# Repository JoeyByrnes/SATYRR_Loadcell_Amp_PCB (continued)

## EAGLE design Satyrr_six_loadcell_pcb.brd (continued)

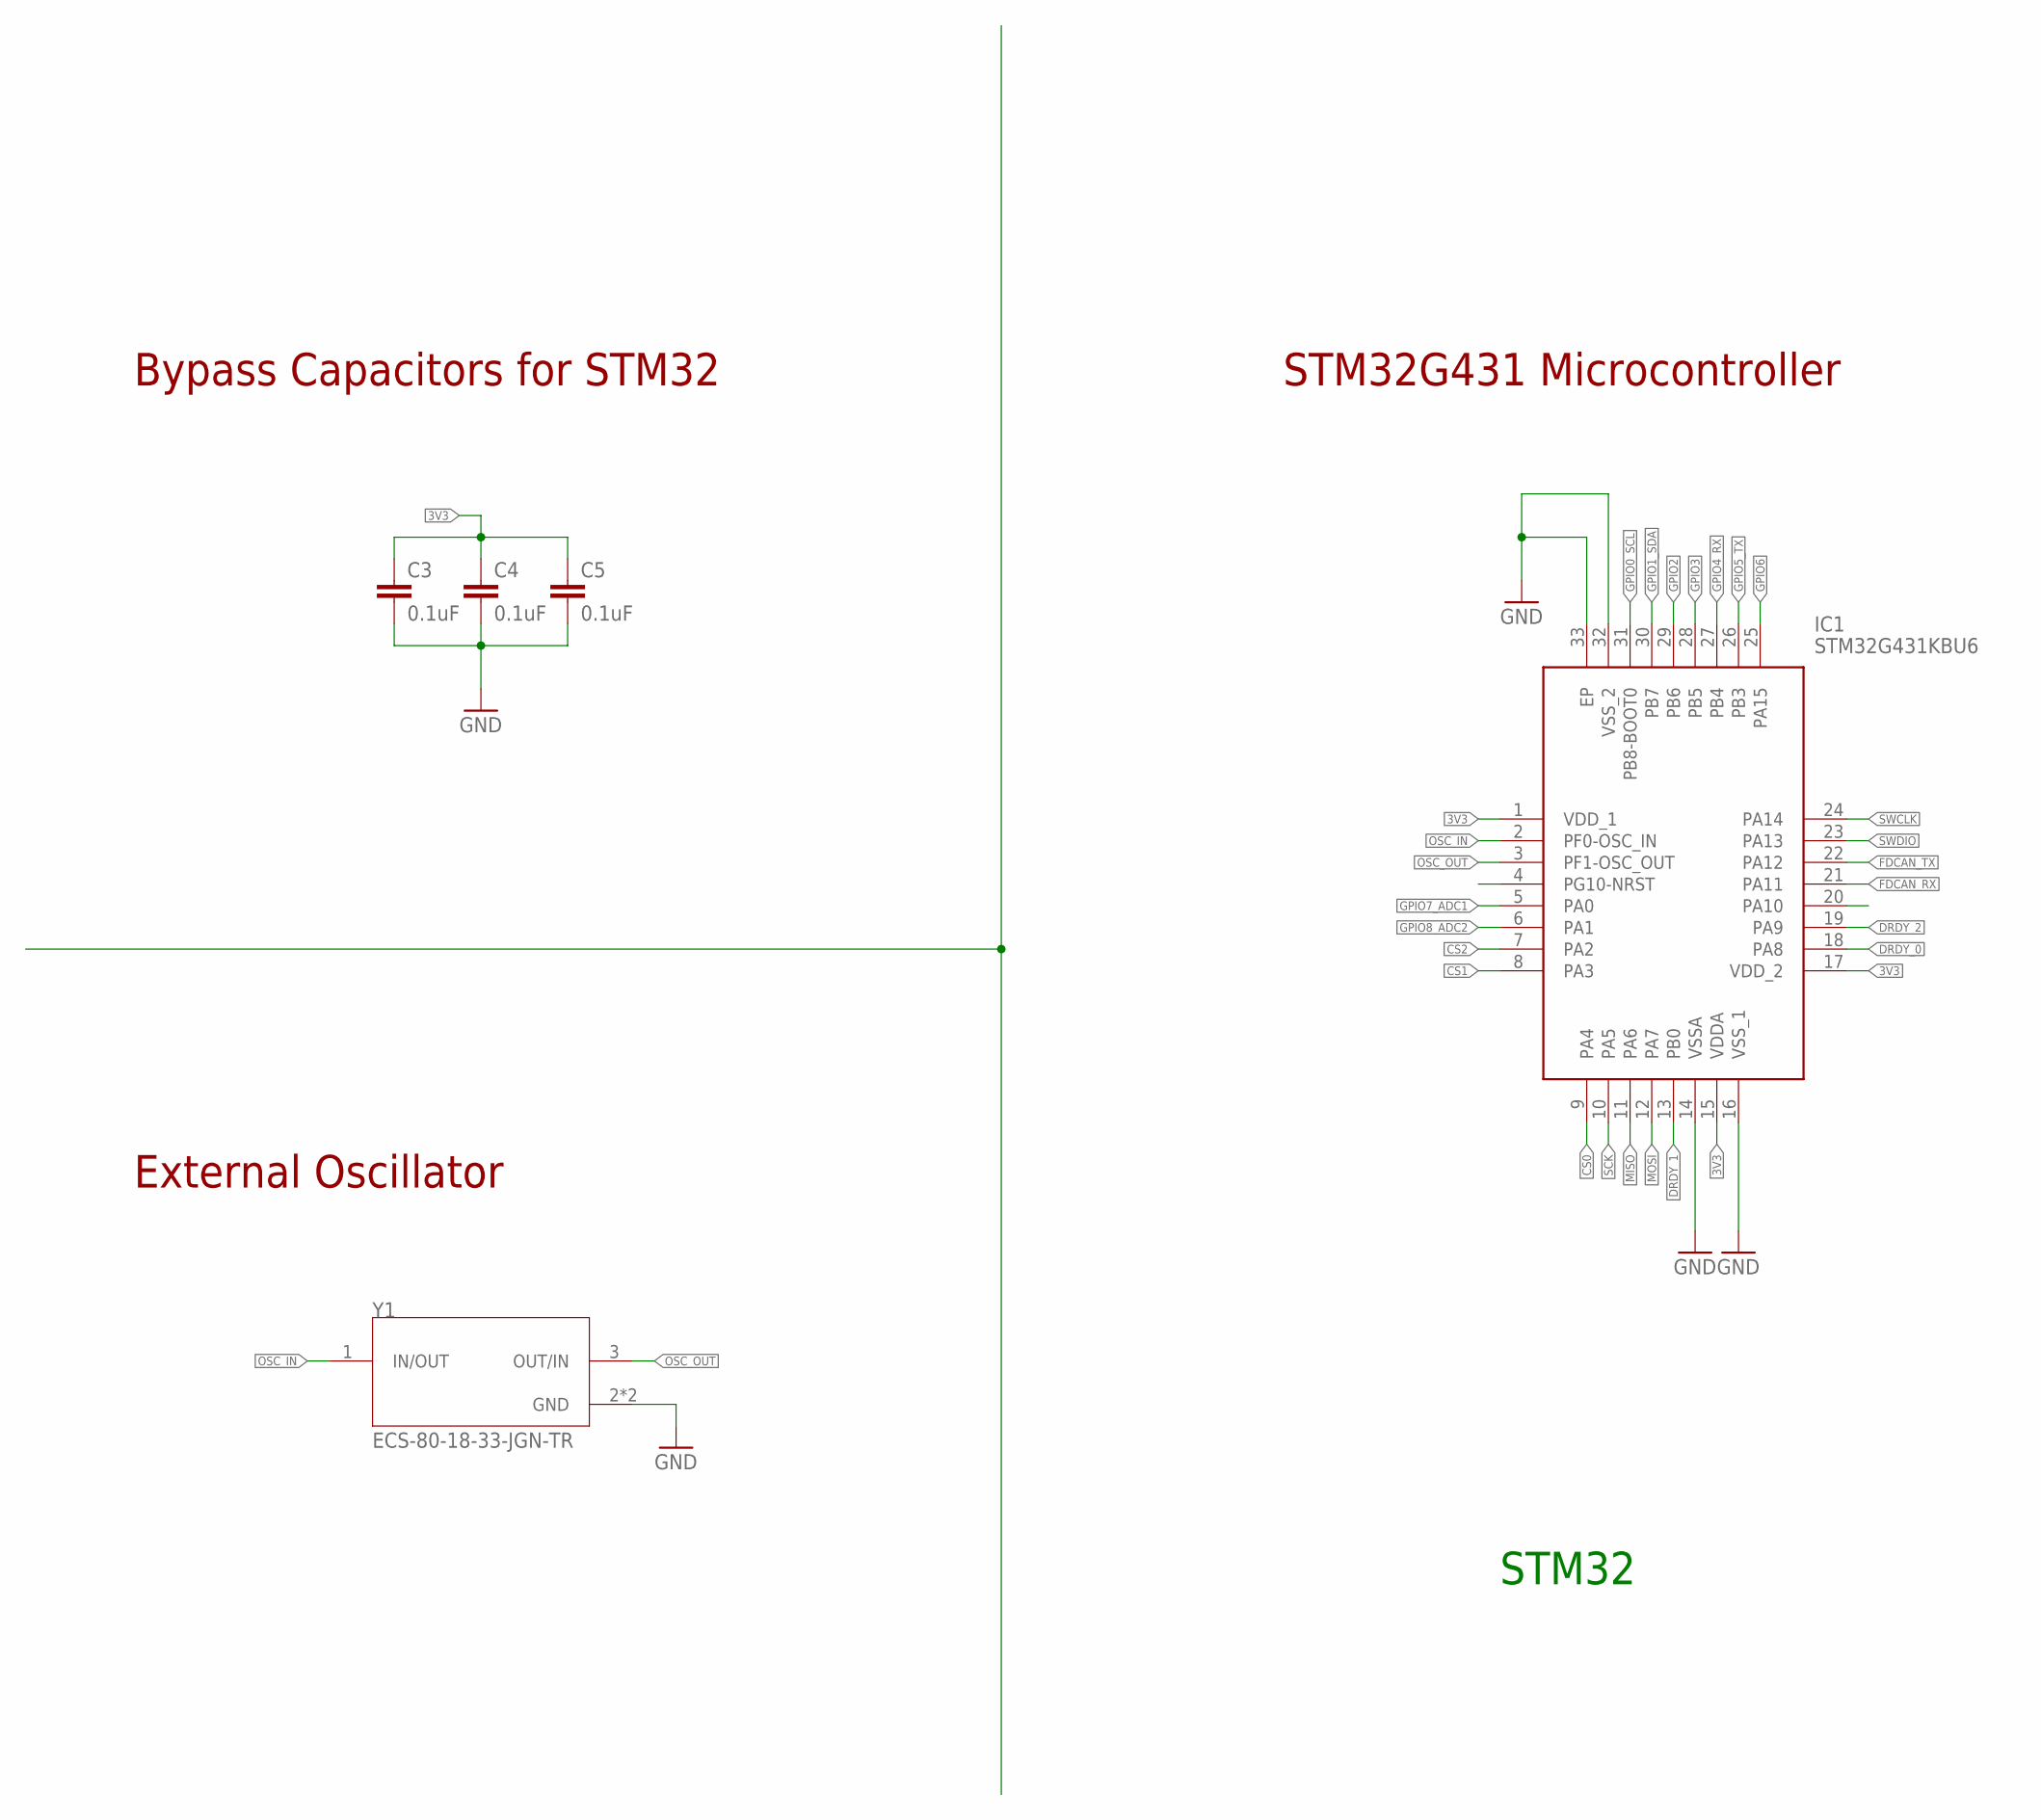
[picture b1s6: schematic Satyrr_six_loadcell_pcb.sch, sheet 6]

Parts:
C3, C4, C5: 0.1uF; C0603
IC1: STM32G431KBU6; QFN50P500X500X60-33N
Y1: ECS-80-18-33-JGN-TR; XTAL_ECS-240-8-33-AGN-TR

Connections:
3V3: C3.1, C4.1, C5.1, IC1.1 (VDD_1), IC1.15 (VDDA), IC1.17 (VDD_2); also elsewhere on the board
CS0: IC1.9 (PA4); also elsewhere on the board
CS1: IC1.8 (PA3); also elsewhere on the board
CS2: IC1.7 (PA2); also elsewhere on the board
DRDY_0: IC1.18 (PA8); also elsewhere on the board
DRDY_1: IC1.13 (PB0); also elsewhere on the board
DRDY_2: IC1.19 (PA9); also elsewhere on the board
FDCAN_RX: IC1.21 (PA11); also elsewhere on the board
FDCAN_TX: IC1.22 (PA12); also elsewhere on the board
GND: C3.2, C4.2, C5.2, IC1.14 (VSSA), IC1.16 (VSS_1), IC1.32 (VSS_2), IC1.33 (EP), Y1.2 (GND), Y1.4 (GND); also elsewhere on the board
GPIO0_SCL: IC1.31 (PB8-BOOT0); also elsewhere on the board
GPIO1_SDA: IC1.30 (PB7); also elsewhere on the board
GPIO2: IC1.29 (PB6); also elsewhere on the board
GPIO3: IC1.28 (PB5); also elsewhere on the board
GPIO4_RX: IC1.27 (PB4); also elsewhere on the board
GPIO5_TX: IC1.26 (PB3); also elsewhere on the board
GPIO6: IC1.25 (PA15); also elsewhere on the board
GPIO7_ADC1: IC1.5 (PA0); also elsewhere on the board
GPIO8_ADC2: IC1.6 (PA1); also elsewhere on the board
MISO: IC1.11 (PA6); also elsewhere on the board
MOSI: IC1.12 (PA7); also elsewhere on the board
OSC_IN: IC1.2 (PF0-OSC_IN), Y1.1 (IN/OUT)
OSC_OUT: IC1.3 (PF1-OSC_OUT), Y1.3 (OUT/IN)
SCK: IC1.10 (PA5); also elsewhere on the board
SWCLK: IC1.24 (PA14); also elsewhere on the board
SWDIO: IC1.23 (PA13); also elsewhere on the board

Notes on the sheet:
Bypass Capacitors for STM32
External Oscillator
STM32G431 Microcontroller
STM32

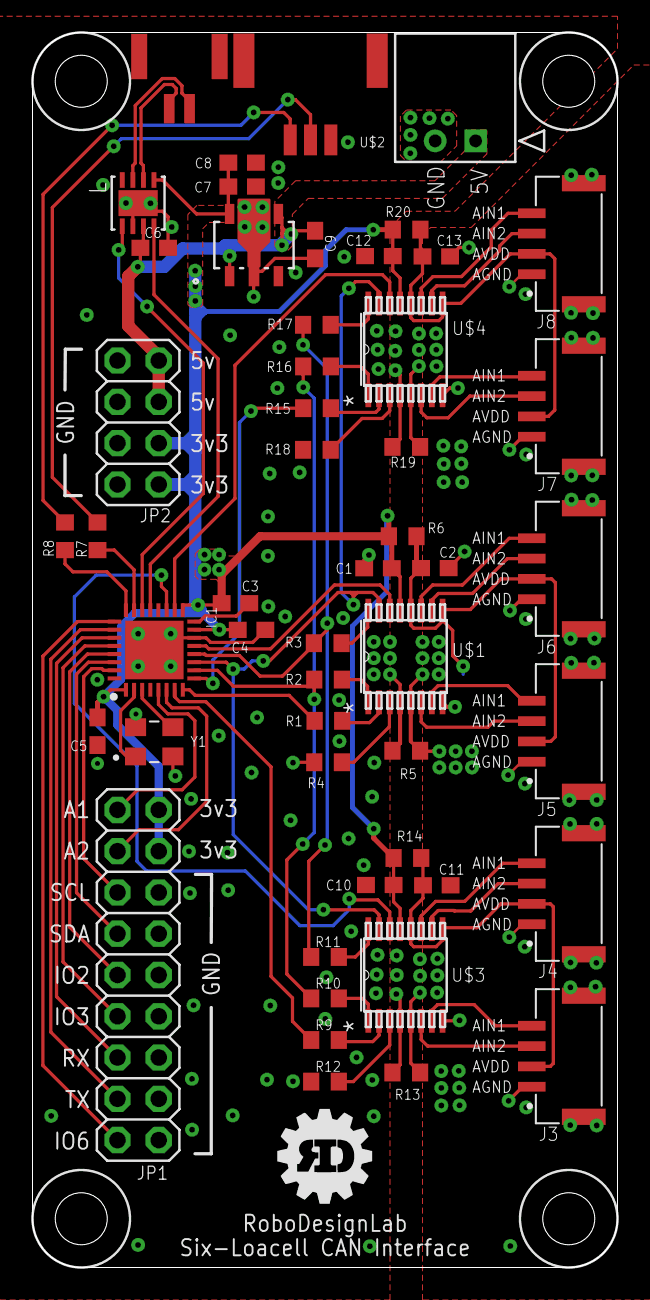
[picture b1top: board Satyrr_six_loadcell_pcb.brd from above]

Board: 4 copper layers, 36.0 x 76.0 mm, 51 parts (0 on the bottom side), 57 nets.

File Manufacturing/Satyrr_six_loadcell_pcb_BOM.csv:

Qty , Value                          , Package                   , Parts                                       , Links
9, 0R                             , R0603                     , R4  R5  R6  R12  R13  R14  R18  R19  R20    , https://www.digikey.com/en/products/detail/stackpole-electro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
10, 0.1uF                          , C0603                     , C1  C2  C10  C11  C12  C13  C3  C4  C5  C6  , https://www.digikey.com/en/products/detail/samsung-electro-m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
2, 10uF                           , C0603                     , C8  C9                                      , https://www.digikey.com/en/products/detail/taiyo-yuden/LMK10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
1, 125SH-G-03-TR-SMT              , 125SH-G-03-TR-SMT         , U$2                                         , https://www.digikey.com/en/products/detail/adam-tech/125SH-G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 
1,22057025, CON_22057025_MOL          , J9                                          , https://www.digikey.com/en/products/detail/molex/0022057025/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
2, 22R                            , R0603                     , R7  R8                                      , https://www.digikey.com/en/products/detail/te-connectivity-p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
1, 4.7uF                          , C0603                     , C7                                          , https://www.digikey.com/en/products/detail/taiyo-yuden/LMK10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
9, 47R                            , R0603                     , R1  R2  R3  R9  R10  R11  R15  R16  R17     , https://www.digikey.com/en/products/detail/walsin-technology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
3, ADS1220                        , TSSOP-16                  , U$1  U$3  U$4                               , https://www.mouser.com/ProductDetail/Texas-Instruments/ADS12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
1, AP7361C-33Y5-13SOT89-5_DIO-M   , SOT89-5_DIO-M             , U2                                          , https://www.digikey.com/en/products/detail/diodes-incorporat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
1, ECS-80-18-33-JGN-TR            , XTAL_ECS-240-8-33-AGN-TR  , Y1                                          , https://www.digikey.com/en/products/detail/ecs-inc/ECS-80-18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
1, MCP2562FD-H/MFDFN8_3X3MC_MCH-M , DFN8_3X3MC_MCH-M          , U1                                          , https://www.newark.com/microchip/mcp2562fd-h-sn/can-transcei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
1, SM02BGHSTBLFSN                 , CONN_SM02BGHSTB_JST       , J2                                          , https://www.digikey.com/en/products/detail/jst-sales-america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
6, SM04B-GHS-TB(LF)(SN)-          , JST_SM04B-GHS-TB(LF)(SN)- , J3  J4  J5  J6  J7  J8                      , https://www.digikey.com/en/products/detail/jst-sales-america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
1, STM32G431KBU6                  , QFN50P500X500X60-33N      , IC1                                         , https://www.digikey.com/en/products/detail/stmicroelectronic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

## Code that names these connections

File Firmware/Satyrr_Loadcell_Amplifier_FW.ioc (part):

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Mcu.Name=STM32G431K(6-8-B)Ux
Mcu.Package=UFQFPN32
Mcu.UserName=STM32G431KBUx
PA0.Mode=IN1-Differential
PA0.Signal=ADC1_IN1
PA1.Mode=IN1-Differential
PA1.Signal=ADC1_IN2
PA11.Mode=FDCAN_Activate
PA11.Signal=FDCAN1_RX
PA12.Mode=FDCAN_Activate
PA12.Signal=FDCAN1_TX
PA13.Mode=Serial_Wire
PA13.Signal=SYS_JTMS-SWDIO
PA14.Mode=Serial_Wire
PA14.Signal=SYS_JTCK-SWCLK
PA15.Signal=GPIO_Output
PA2.Signal=GPIO_Output
PA3.Signal=GPIO_Output
PA4.Signal=GPIO_Output
PA5.Mode=Full_Duplex_Master
PA5.Signal=SPI1_SCK
PA6.Mode=Full_Duplex_Master
PA6.Signal=SPI1_MISO
PA7.Mode=Full_Duplex_Master
PA7.Signal=SPI1_MOSI
PA8.Signal=GPIO_Input
PA9.Signal=GPIO_Input
PB0.Signal=GPIO_Input
PB3.Mode=Asynchronous
PB3.Signal=USART2_TX
PB4.Mode=Asynchronous
PB4.Signal=USART2_RX
PB5.Signal=GPIO_Output
PB6.Signal=GPIO_Output
PB7.Signal=I2C1_SDA
PB8-BOOT0.Signal=I2C1_SCL
PF0-OSC_IN.Mode=HSE-External-Oscillator
PF0-OSC_IN.Signal=RCC_OSC_IN
PF1-OSC_OUT.Mode=HSE-External-Oscillator
PF1-OSC_OUT.Signal=RCC_OSC_OUT
RCC.HSE_VALUE=8000000
RCC.SYSCLKFreq_VALUE=170000000
RCC.SYSCLKSource=RCC_SYSCLKSOURCE_PLLCLK
board=custom

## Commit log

2023-06-07 in progress. needs silkscreen and gpio headers
2023-06-07 board finished, ready for design review
2023-06-07 edited readme
2023-06-14 schemetic design review complete
2023-06-14 Full review complete, ready to order
2023-06-14 added 3d model
2023-06-14 updated 3d model
2023-06-14 added BOM
2023-06-16 fixed silkscreen
2023-10-02 updated readme photos
2023-10-02 updated name in readme
2023-10-04 Added firmware
